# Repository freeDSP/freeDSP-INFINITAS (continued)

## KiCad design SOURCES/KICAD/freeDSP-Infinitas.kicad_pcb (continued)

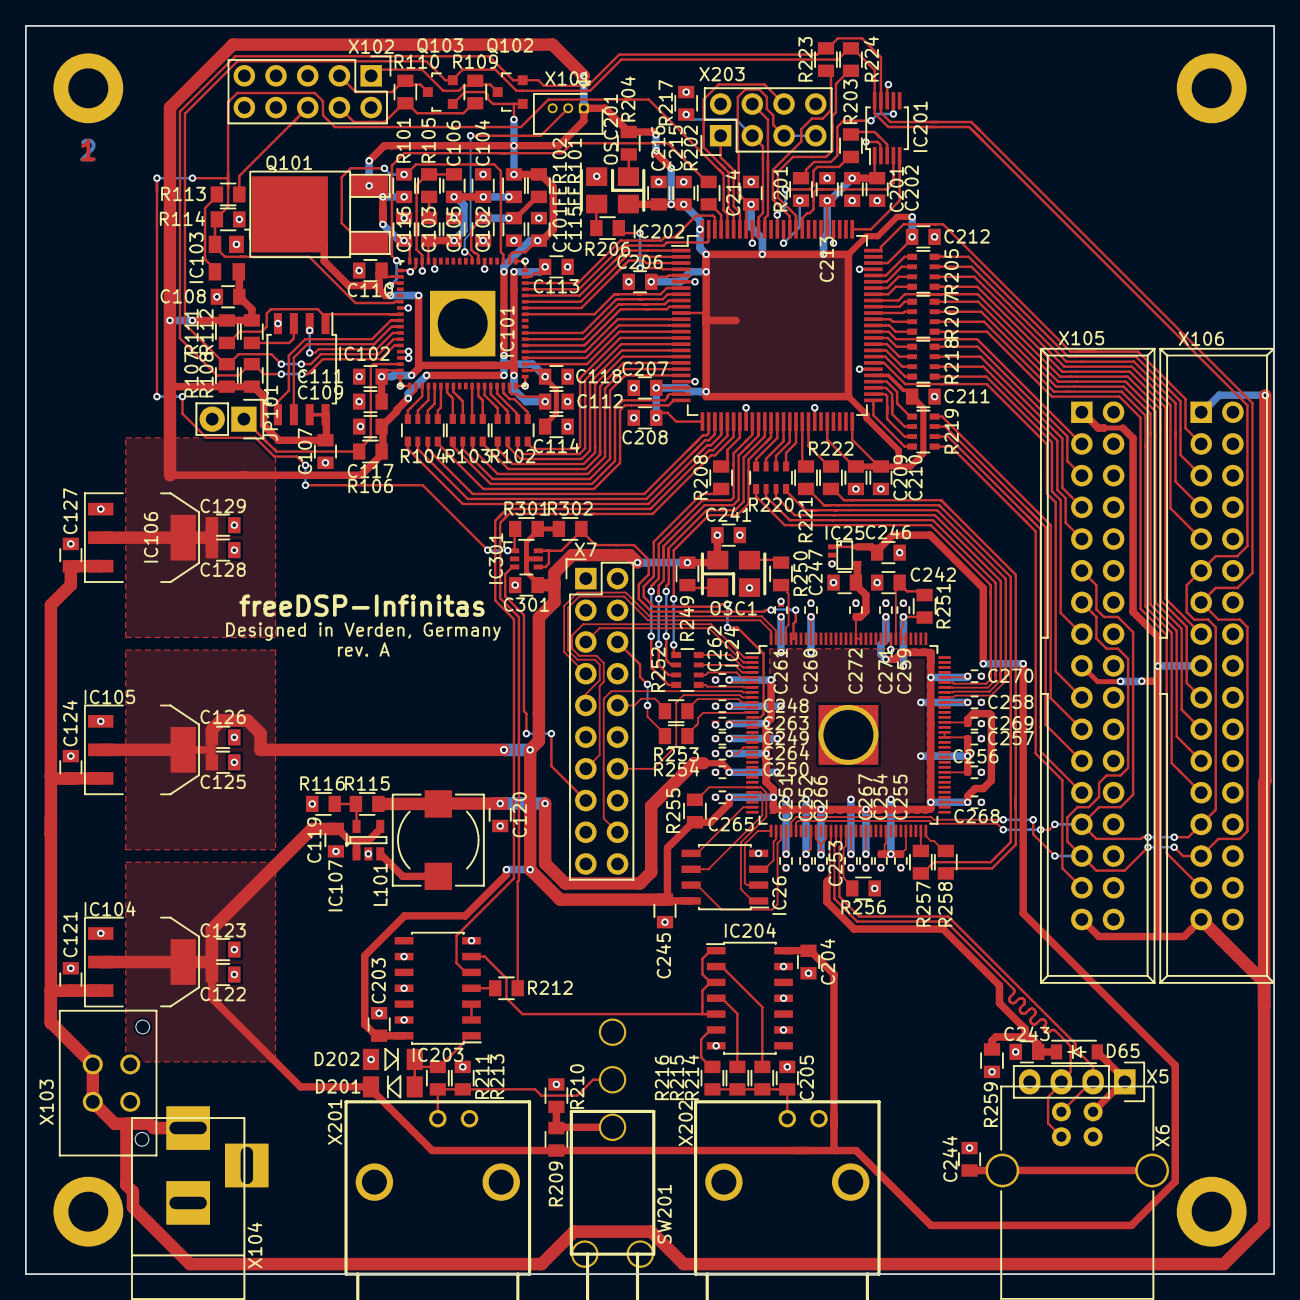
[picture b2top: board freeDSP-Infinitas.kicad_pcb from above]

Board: 2 copper layers, 100.0 x 100.0 mm, 175 parts (0 on the bottom side), 183 nets.

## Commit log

2018-05-30 First PCB layout in 'freeDSP style'
2018-05-30 Added VHDL code
2018-05-30 Added XMOS code
2018-05-30 New PCB layout
2018-05-30 Prototype with 2x freeDSPx-BAL-IO-x8 on same panel
2018-05-30 Updated license
2018-05-30 Added BOM
2018-06-08 Updated Lattice project for bigger MachXO2
2018-06-22 Add i2c configuration of AK4458
    Notice the hack of the i2c modules (LICENSE OF XMOS STUFF IS UNCLEAR)
2018-06-23 TDM Protocol adapted for XMOS -> AK4458
2018-08-01 Bugfix on i2c multiplexer
2018-08-01 Reset forwarded to FPGA
2018-09-04 Changed USBi connector
2018-09-04 Updated BOM
2018-09-05 Upgraded to KiCAD 5
2018-09-19 Exported Gerbers
2018-10-12 Bugfix on Silkscreen
2018-10-14 Updated VHDL code
2018-10-14 Documentation
2018-10-16 New Gerber export
2018-10-17 Added missing parts
2021-01-21 Documentation exported to Word and RTF for extraction of images
2021-03-12 Added link to Documentation in GoogleDocs
2021-03-12 Added Application note on multichannel audio setup
